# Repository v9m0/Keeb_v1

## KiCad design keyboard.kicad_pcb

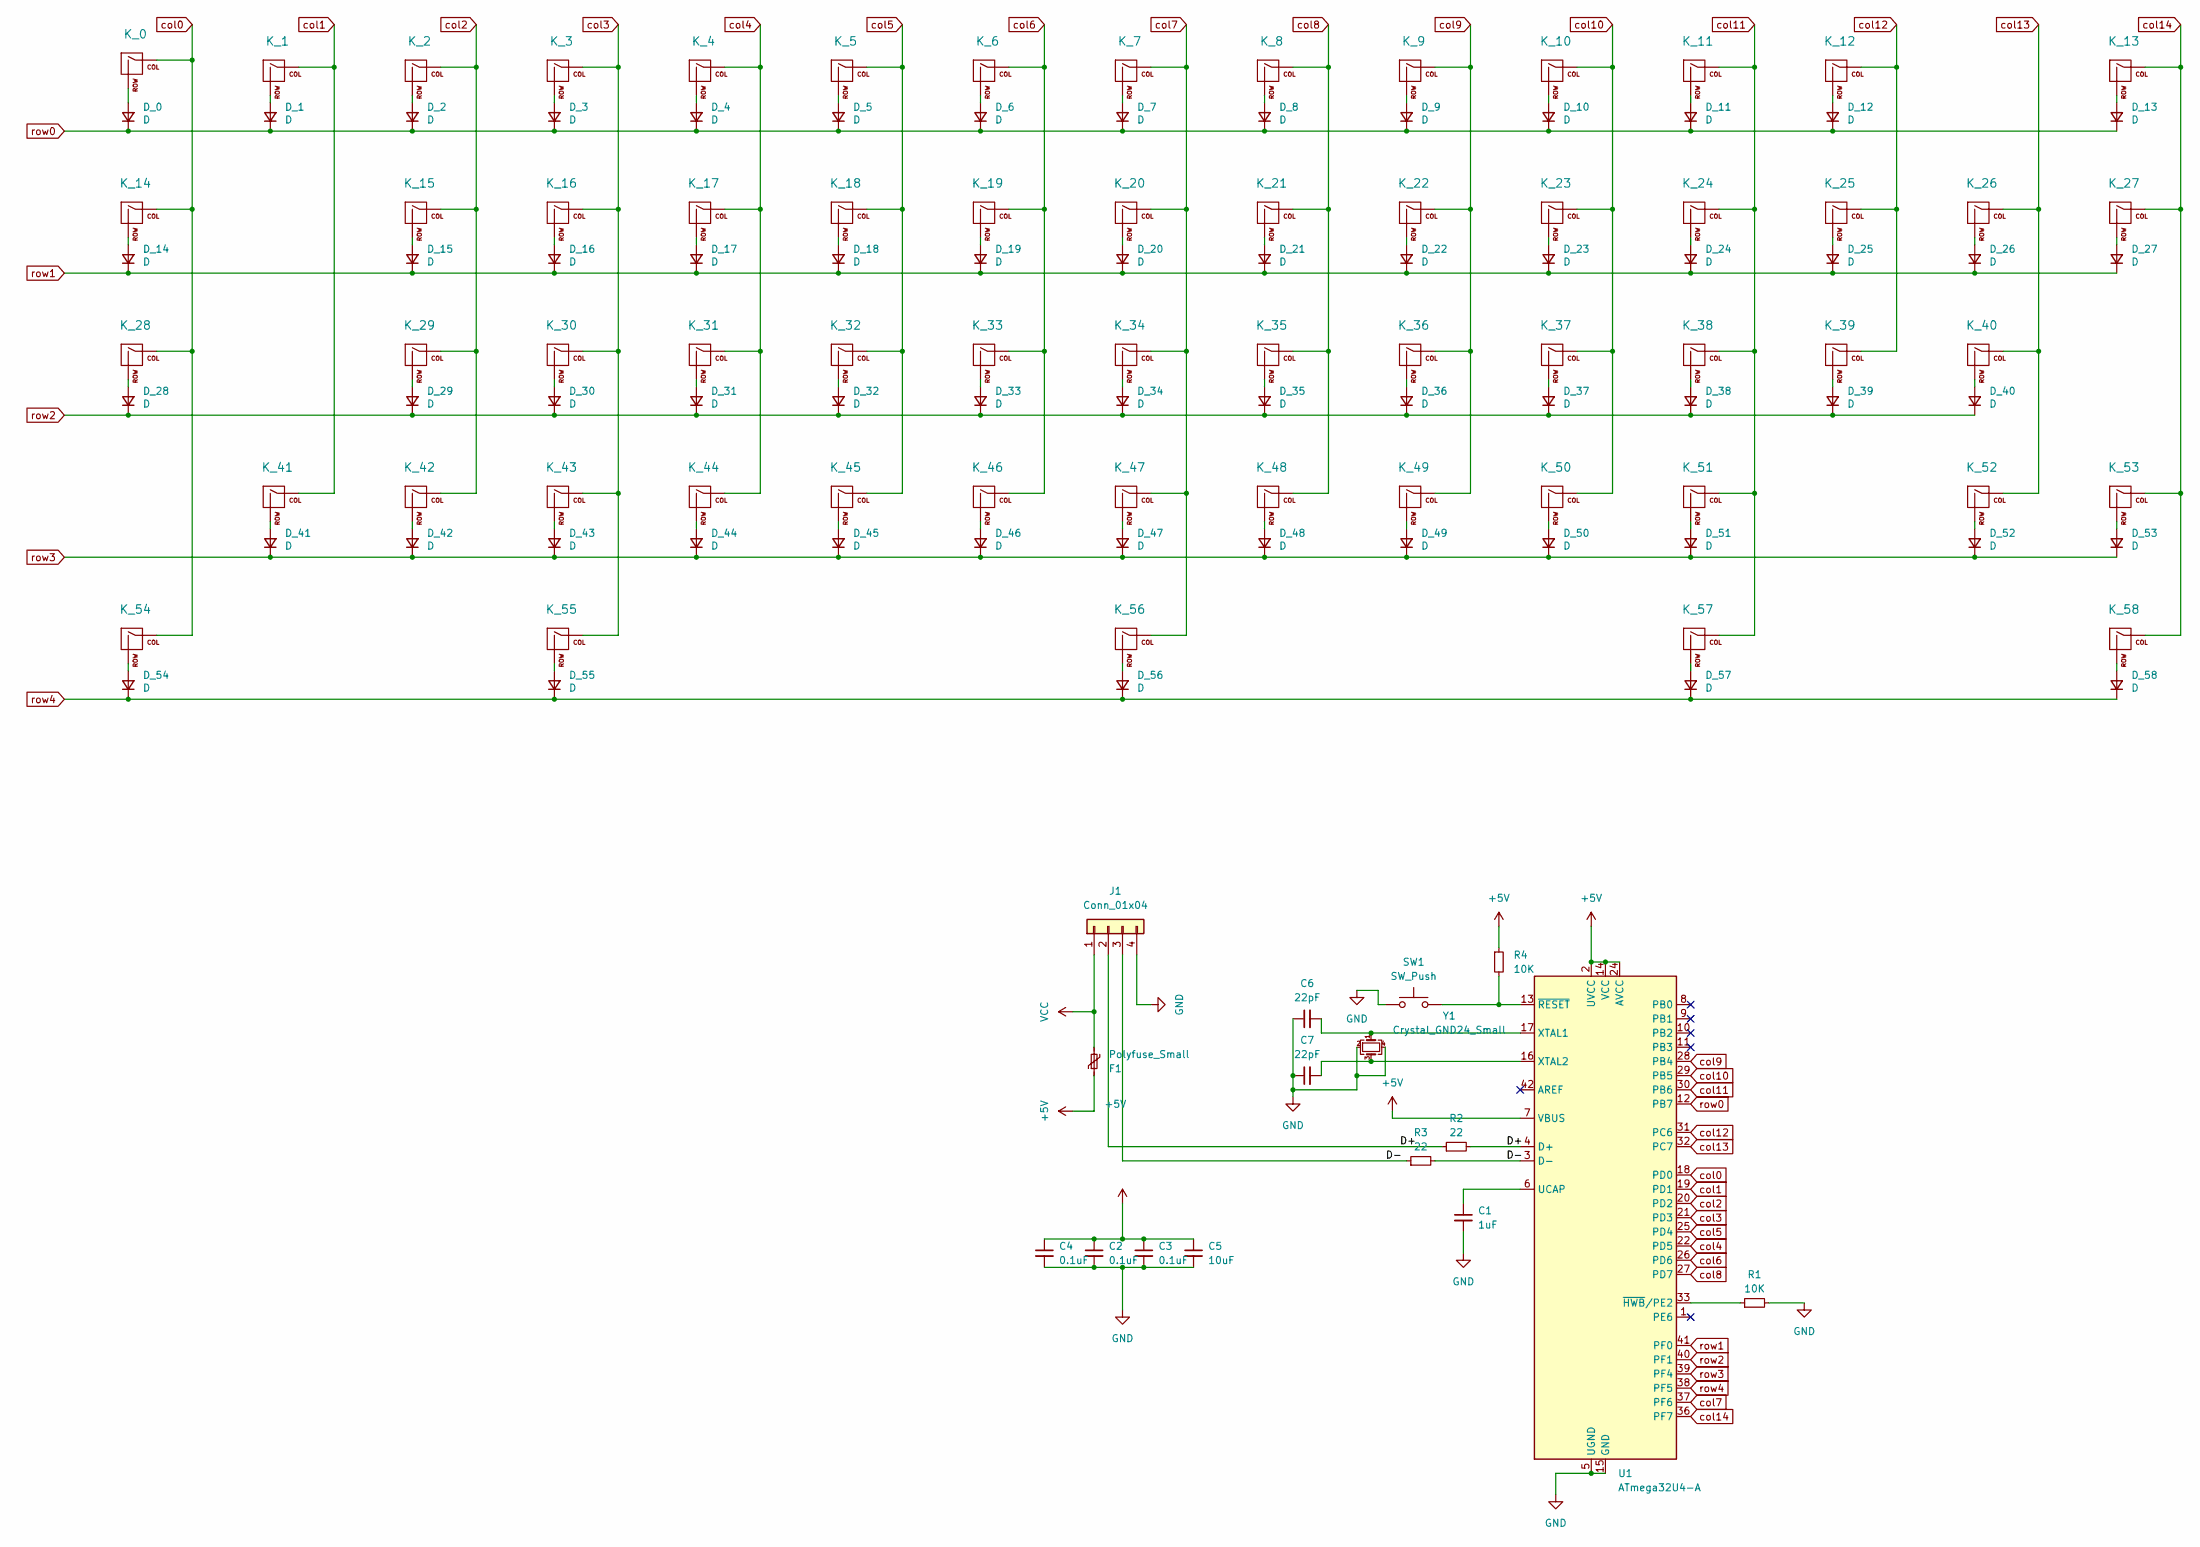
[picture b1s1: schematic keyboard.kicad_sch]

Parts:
C1: 1uF; C_0805_2012Metric
C2, C3, C4: 0.1uF; C_0805_2012Metric
C5: 10uF; C_0805_2012Metric
C6, C7: 22pF; C_0805_2012Metric
D_0, D_1, D_2, D_3, D_4, D_5, D_6, D_7, D_8, D_9, D_10, D_11, D_12, D_13, D_14, D_15, D_16, D_17, D_18, D_19, D_20, D_21, D_22, D_23, D_24, D_25, D_26, D_27, D_28, D_29, D_30, D_31, D_32, D_33, D_34, D_35, D_36, D_37, D_38, D_39, D_40, D_41, D_42, D_43, D_44, D_45, D_46, D_47, D_48, D_49, D_50, D_51, D_52, D_53, D_54, D_55, D_56, D_57, D_58: D; D_SOD-123
F1: Polyfuse_Small; Fuse_1206_3216Metric
J1: Conn_01x04; JST_SH_SM04B-SRSS-TB_1x04-1MP_P1.00mm_Horizontal
K_0, K_1, K_2, K_3, K_4, K_5, K_6, K_7, K_8, K_9, K_10, K_11, K_12, K_15, K_16, K_17, K_18, K_19, K_20, K_21, K_22, K_23, K_24, K_25, K_26, K_29, K_30, K_31, K_32, K_33, K_34, K_35, K_36, K_37, K_38, K_39, K_42, K_43, K_44, K_45, K_46, K_47, K_48, K_49, K_50, K_51, K_53: KEYSW; MXOnly-1U-NoLED
K_13: KEYSW; MXOnly-2U-NoLED
K_14, K_27: KEYSW; MXOnly-1.5U-NoLED
K_28, K_52: KEYSW; MXOnly-1.75U-NoLED
K_40, K_41: KEYSW; MXOnly-2.25U-NoLED
K_54, K_55, K_57, K_58: KEYSW; MXOnly-1.25U-NoLED
K_56: KEYSW; MXOnly-7U-ReversedStabilizers-NoLED
R1, R4: 10K; R_0805_2012Metric
R2, R3: 22; R_0805_2012Metric
SW1: SW_Push; SKQG-1155865
U1: ATmega32U4-A; TQFP-44_10x10mm_P0.8mm
Y1: Crystal_GND24_Small; Crystal_SMD_3225-4Pin_3.2x2.5mm

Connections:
+5V: C2.1, C3.1, C4.1, C5.1, F1.1, R4.1, U1.2 (UVCC), U1.7 (VBUS), U1.14 (VCC), U1.24 (AVCC), U1.34 (VCC), U1.44 (AVCC)
/D+: J1.2, R2.1, R2.2, U1.4 (D+)
/D-: J1.3, R3.1, R3.2, U1.3 (D-)
GND: C1.2, C2.2, C3.2, C4.2, C5.2, C6.1, C7.1, J1.4, R1.2, SW1.1, U1.5 (UGND), U1.15 (GND), U1.23 (GND), U1.35 (GND), U1.43 (GND), Y1.2, Y1.4
unnamed: D_0.2 (A), K_0.2 (ROW)
unnamed: D_1.2 (A), K_1.2 (ROW)
unnamed: D_2.2 (A), K_2.2 (ROW)
unnamed: D_3.2 (A), K_3.2 (ROW)
unnamed: D_4.2 (A), K_4.2 (ROW)
unnamed: D_5.2 (A), K_5.2 (ROW)
unnamed: D_6.2 (A), K_6.2 (ROW)
unnamed: D_7.2 (A), K_7.2 (ROW)
unnamed: D_8.2 (A), K_8.2 (ROW)
unnamed: D_9.2 (A), K_9.2 (ROW)
unnamed: D_10.2 (A), K_10.2 (ROW)
unnamed: D_11.2 (A), K_11.2 (ROW)
unnamed: D_12.2 (A), K_12.2 (ROW)
unnamed: D_13.2 (A), K_13.2 (ROW)
unnamed: D_14.2 (A), K_14.2 (ROW)
unnamed: D_15.2 (A), K_15.2 (ROW)
unnamed: D_16.2 (A), K_16.2 (ROW)
unnamed: D_17.2 (A), K_17.2 (ROW)
unnamed: D_18.2 (A), K_18.2 (ROW)
unnamed: D_19.2 (A), K_19.2 (ROW)
unnamed: D_20.2 (A), K_20.2 (ROW)
unnamed: D_21.2 (A), K_21.2 (ROW)
unnamed: D_22.2 (A), K_22.2 (ROW)
unnamed: D_23.2 (A), K_23.2 (ROW)
unnamed: D_24.2 (A), K_24.2 (ROW)
unnamed: D_25.2 (A), K_25.2 (ROW)
unnamed: D_26.2 (A), K_26.2 (ROW)
unnamed: D_27.2 (A), K_27.2 (ROW)
unnamed: D_28.2 (A), K_28.2 (ROW)
unnamed: D_29.2 (A), K_29.2 (ROW)
unnamed: D_30.2 (A), K_30.2 (ROW)
unnamed: D_31.2 (A), K_31.2 (ROW)
unnamed: D_32.2 (A), K_32.2 (ROW)
unnamed: D_33.2 (A), K_33.2 (ROW)
unnamed: D_34.2 (A), K_34.2 (ROW)
unnamed: D_35.2 (A), K_35.2 (ROW)
unnamed: D_36.2 (A), K_36.2 (ROW)
unnamed: D_37.2 (A), K_37.2 (ROW)
unnamed: D_38.2 (A), K_38.2 (ROW)
unnamed: D_39.2 (A), K_39.2 (ROW)
unnamed: D_40.2 (A), K_40.2 (ROW)
unnamed: D_41.2 (A), K_41.2 (ROW)
unnamed: D_42.2 (A), K_42.2 (ROW)
unnamed: D_43.2 (A), K_43.2 (ROW)
unnamed: D_44.2 (A), K_44.2 (ROW)
unnamed: D_45.2 (A), K_45.2 (ROW)
unnamed: D_46.2 (A), K_46.2 (ROW)
unnamed: D_47.2 (A), K_47.2 (ROW)
unnamed: D_48.2 (A), K_48.2 (ROW)
unnamed: D_49.2 (A), K_49.2 (ROW)
unnamed: D_50.2 (A), K_50.2 (ROW)
unnamed: D_51.2 (A), K_51.2 (ROW)
unnamed: D_52.2 (A), K_52.2 (ROW)
unnamed: D_53.2 (A), K_53.2 (ROW)
unnamed: D_54.2 (A), K_54.2 (ROW)
unnamed: D_55.2 (A), K_55.2 (ROW)
unnamed: D_56.2 (A), K_56.2 (ROW)
unnamed: D_57.2 (A), K_57.2 (ROW)
unnamed: D_58.2 (A), K_58.2 (ROW)
unnamed: C1.1, U1.6 (UCAP)
unnamed: C6.2, U1.17 (XTAL1), Y1.1
unnamed: C7.2, U1.16 (XTAL2), Y1.3
unnamed: R1.1, U1.33 (~HWB/PE2)
unnamed: R4.2, SW1.2, U1.13 (~RESET)
VCC: F1.2, J1.1
col0: K_0.1 (COL), K_14.1 (COL), K_28.1 (COL), K_54.1 (COL), U1.18 (PD0)
col1: K_1.1 (COL), K_41.1 (COL), U1.19 (PD1)
col2: K_2.1 (COL), K_15.1 (COL), K_29.1 (COL), K_42.1 (COL), U1.20 (PD2)
col3: K_3.1 (COL), K_16.1 (COL), K_30.1 (COL), K_43.1 (COL), K_55.1 (COL), U1.21 (PD3)
col4: K_4.1 (COL), K_17.1 (COL), K_31.1 (COL), K_44.1 (COL), U1.22 (PD5)
col5: K_5.1 (COL), K_18.1 (COL), K_32.1 (COL), K_45.1 (COL), U1.25 (PD4)
col6: K_6.1 (COL), K_19.1 (COL), K_33.1 (COL), K_46.1 (COL), U1.26 (PD6)
col7: K_7.1 (COL), K_20.1 (COL), K_34.1 (COL), K_47.1 (COL), K_56.1 (COL), U1.37 (PF6)
col8: K_8.1 (COL), K_21.1 (COL), K_35.1 (COL), K_48.1 (COL), U1.27 (PD7)
col9: K_9.1 (COL), K_22.1 (COL), K_36.1 (COL), K_49.1 (COL), U1.28 (PB4)
col10: K_10.1 (COL), K_23.1 (COL), K_37.1 (COL), K_50.1 (COL), U1.29 (PB5)
col11: K_11.1 (COL), K_24.1 (COL), K_38.1 (COL), K_51.1 (COL), K_57.1 (COL), U1.30 (PB6)
col12: K_12.1 (COL), K_25.1 (COL), K_39.1 (COL), U1.31 (PC6)
col13: K_26.1 (COL), K_40.1 (COL), K_52.1 (COL), U1.32 (PC7)
col14: K_13.1 (COL), K_27.1 (COL), K_53.1 (COL), K_58.1 (COL), U1.36 (PF7)
row0: D_0.1 (K), D_1.1 (K), D_2.1 (K), D_3.1 (K), D_4.1 (K), D_5.1 (K), D_6.1 (K), D_7.1 (K), D_8.1 (K), D_9.1 (K), D_10.1 (K), D_11.1 (K), D_12.1 (K), D_13.1 (K), U1.12 (PB7)
row1: D_14.1 (K), D_15.1 (K), D_16.1 (K), D_17.1 (K), D_18.1 (K), D_19.1 (K), D_20.1 (K), D_21.1 (K), D_22.1 (K), D_23.1 (K), D_24.1 (K), D_25.1 (K), D_26.1 (K), D_27.1 (K), U1.41 (PF0)
row2: D_28.1 (K), D_29.1 (K), D_30.1 (K), D_31.1 (K), D_32.1 (K), D_33.1 (K), D_34.1 (K), D_35.1 (K), D_36.1 (K), D_37.1 (K), D_38.1 (K), D_39.1 (K), D_40.1 (K), U1.40 (PF1)
row3: D_41.1 (K), D_42.1 (K), D_43.1 (K), D_44.1 (K), D_45.1 (K), D_46.1 (K), D_47.1 (K), D_48.1 (K), D_49.1 (K), D_50.1 (K), D_51.1 (K), D_52.1 (K), D_53.1 (K), U1.39 (PF4)
row4: D_54.1 (K), D_55.1 (K), D_56.1 (K), D_57.1 (K), D_58.1 (K), U1.38 (PF5)

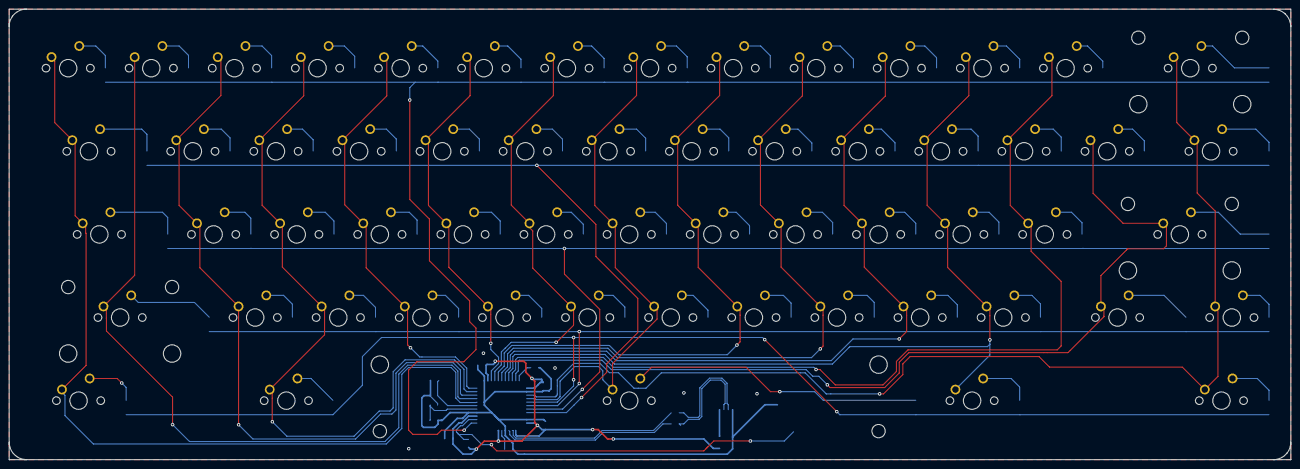
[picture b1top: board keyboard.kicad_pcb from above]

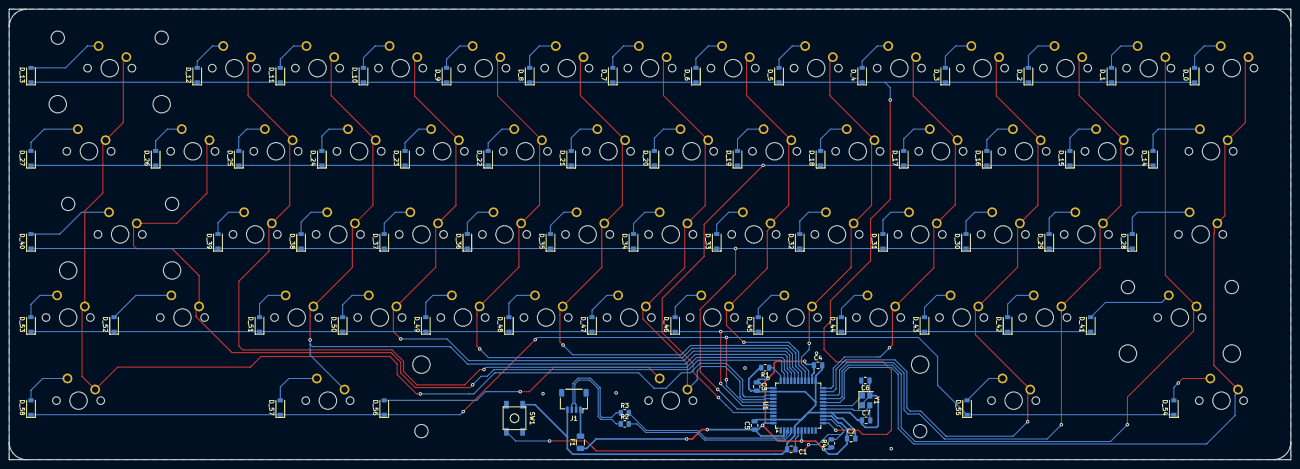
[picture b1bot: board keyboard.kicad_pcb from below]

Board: 2 copper layers, 293.8 x 103.2 mm, 134 parts (75 on the bottom side), 89 nets.

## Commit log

2024-03-21 Adding files
2024-03-29 Added gitignore file
2024-03-29 gitignore setup
